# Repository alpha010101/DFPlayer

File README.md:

###
市販されているMP3プレイヤーユニット"DFPlayer mini"2個を載せるための基板。外部のマイコンからUARTでコマンドを送って操作することを想定。UARTの接続はPHコネクタ。

基板上のスイッチは「Start/Pause」「Next/Volum+」「Prev/Volume-」の3種類を2系統それぞれに設ける。この制御用の端子は外に引き出せるようなパターンになっている。出力はDFPlayer-miniに載っているアンプを通したモノラル出力をスピーカー端子に、アンプを通さないDACのステレオ出力を3.5mmステレオジャックに出している。この基板に電源を入れれば単体で動作する。基板上は電源が5Vとなっているが、搭載されているICとしては3.3Vが正しいので注意を（5Vはほぼ仕様上の限界で、4.8Vくらいに留めるほうが良いとも言われている）

テスト用に集めたDFPlayer-miniだが、1個は以前に秋月で買ったもの、1個は今回秋月で買ったもの、2個は今回Amazonで買ったもので、3種類ともUARTコマンドに対する動作や、DACの出力や、動作LEDの色など色々と違いがあり、考えていた操作ができなかった。このあたり、まとめる時間があれば追記するかもしれない。

動かしてみた感想としては、ブレッドボードで鳴らすよりかなり音が良く、特にDAC出力の3.5mmステレオジャックからの出力は期待以上の音質であった

SchematicとPCB-LayoutはAutodesk-Eagle無償版で作成し、elecrowで製造することを念頭にガーバーを作成している

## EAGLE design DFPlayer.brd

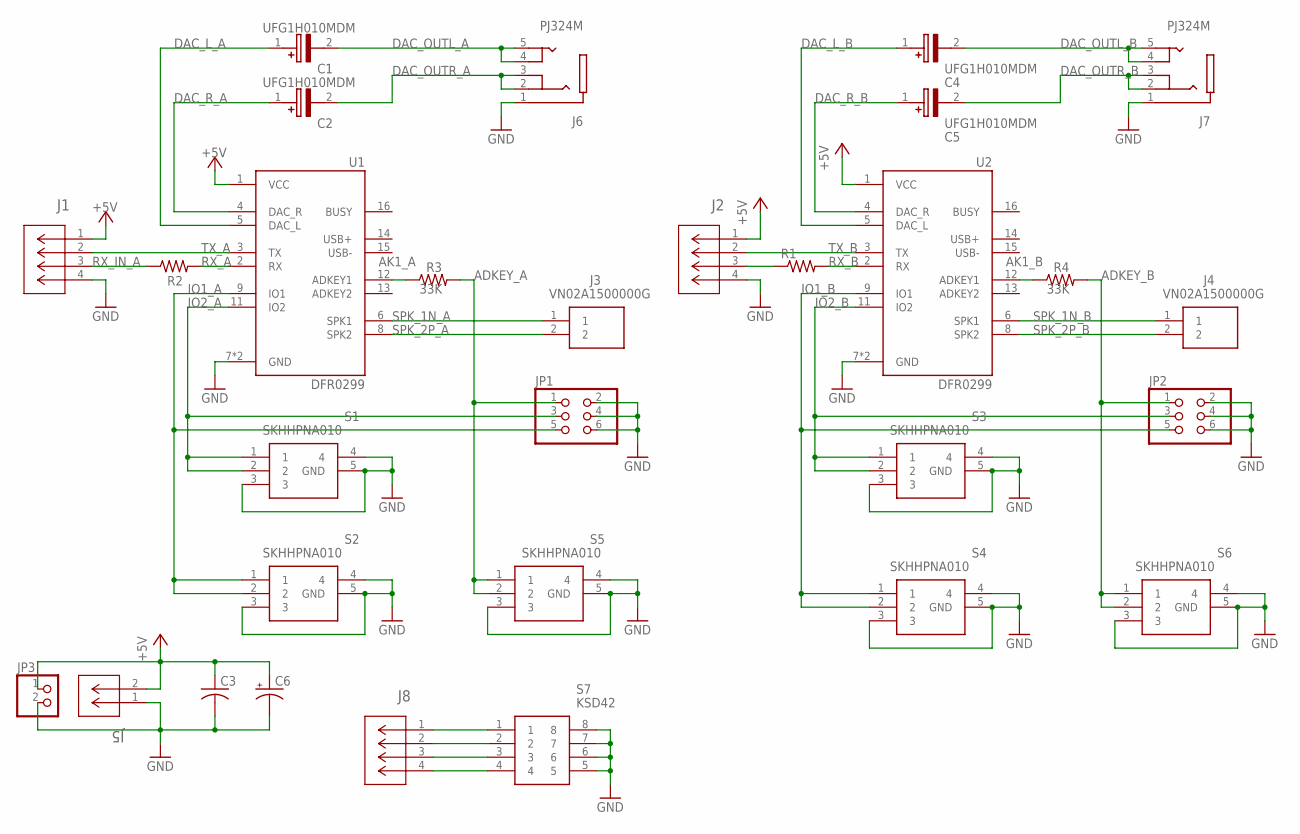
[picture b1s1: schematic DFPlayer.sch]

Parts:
C1, C2, C4, C5: UFG1H010MDM; CAPPRD200W60D550H1250
C3: C-US025-024X044; C025-024X044
C6: CPOL-USB45181A; B45181A
J1, J2, J8: S4B-PH-K-S(LF)(SN); CONN_S4B-PH-K-S_JST
J3, J4: VN02A1500000G
J5: S2B-PH-K-S(LF)(SN); CONN_S2B-PH-K-S_JST
J6, J7: PJ324M; WENZHOU_PJ324M
JP1, JP2: PINHD-2X3; 2X03
JP3: PINHD-1X2; 1X02
R1, R2, R3, R4: R-US_0204/7; 0204/7
S1, S2, S3, S4, S5, S6: SKHHPNA010; SKHHPJA010
S7: KSD42; DIP815W60P254L1210H450Q8N
U1, U2: DFR0299; MODULE_DFR0299

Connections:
+5V: C3.1, C6.+, J1.1, J2.1, J5.2, JP3.1, U1.1 (VCC), U2.1 (VCC)
ADKEY_A: JP1.1, R3.2, S5.1, S5.2
ADKEY_B: JP2.1, R4.2, S6.1, S6.2
AK1_A: R3.1, U1.12 (ADKEY1)
AK1_B: R4.1, U2.12 (ADKEY1)
DAC_L_A: C1.1 (+), U1.5 (DAC_L)
DAC_L_B: C4.1 (+), U2.5 (DAC_L)
DAC_OUTL_A: C1.2 (-), J6.4 (TIP_1), J6.5 (TIP_2)
DAC_OUTL_B: C4.2 (-), J7.4 (TIP_1), J7.5 (TIP_2)
DAC_OUTR_A: C2.2 (-), J6.2 (RING_1), J6.3 (RING_2)
DAC_OUTR_B: C5.2 (-), J7.2 (RING_1), J7.3 (RING_2)
DAC_R_A: C2.1 (+), U1.4 (DAC_R)
DAC_R_B: C5.1 (+), U2.4 (DAC_R)
GND: C3.2, C6.-, J1.4, J2.4, J5.1, J6.1 (SLEEVE), J7.1 (SLEEVE), JP1.2, JP1.4, JP1.6, JP2.2, JP2.4, JP2.6, JP3.2, S1.3, S1.4, S1.5 (GND), S2.3, S2.4, S2.5 (GND), S3.3, S3.4, S3.5 (GND), S4.3, S4.4, S4.5 (GND), S5.3, S5.4, S5.5 (GND), S6.3, S6.4, S6.5 (GND), S7.5, S7.6, S7.7, S7.8, U1.7 (GND), U1.10 (GND), U2.7 (GND), U2.10 (GND)
IO1_A: JP1.5, S2.1, S2.2, U1.9 (IO1)
IO1_B: JP2.5, S4.1, S4.2, U2.9 (IO1)
IO2_A: JP1.3, S1.1, S1.2, U1.11 (IO2)
IO2_B: JP2.3, S3.1, S3.2, U2.11 (IO2)
unnamed: J8.1, S7.1
unnamed: J8.2, S7.2
unnamed: J8.3, S7.3
unnamed: J8.4, S7.4
unnamed: J2.3, R1.1
RX_A: R2.2, U1.2 (RX)
RX_B: R1.2, U2.2 (RX)
RX_IN_A: J1.3, R2.1
SPK_1N_A: J3.1, U1.6 (SPK1)
SPK_1N_B: J4.1, U2.6 (SPK1)
SPK_2P_A: J3.2, U1.8 (SPK2)
SPK_2P_B: J4.2, U2.8 (SPK2)
TX_A: J1.2, U1.3 (TX)
TX_B: J2.2, U2.3 (TX)

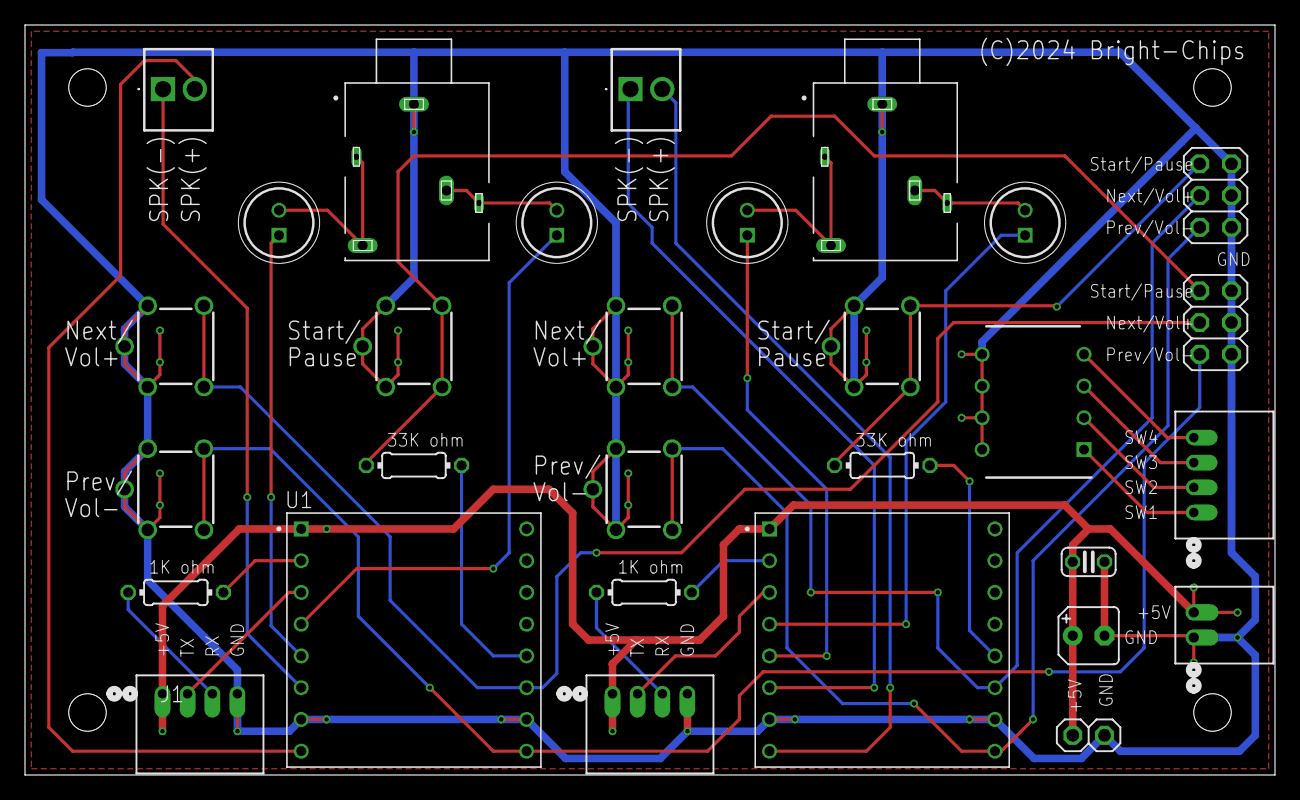
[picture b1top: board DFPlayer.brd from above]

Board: 2 copper layers, 100.0 x 60.0 mm, 30 parts (0 on the bottom side), 32 nets.

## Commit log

2025-01-01 initial release

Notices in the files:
DFPlayer.brd:
(C)2024 Bright-Chips
parts and their libraries:
COPYRIGHT: Copyright (C) 2024 Ultra Librarian. All rights reserved.
